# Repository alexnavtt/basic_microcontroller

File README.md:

# Basic Microcontroller

As the name suggests, this repo contains files and code an educational project of mine to build a microcontroller 
breakout board from scratch. I picked the ATMega32u4 for its native USB status, as well as for the wealth of tutorial
and educational material out there on the web. The board itself doesn't have much of a purpose, though anyone is free 
to use it as a reference for a similar project of their own. 

The board has the following features:
  * ATMega32u4 MCU running at 8 MHz
  * USB-C terminal
  * 6-pin ICSP header terminal
  * 1x ADC screw terminal
  * 1x I2C Stemma/QWIIC header
  * 1x RGB LED
  * 5x5 green LED array

There's no particular reason that I run the board at 8 MHz. Generally this MCU is operated at 16 MHz when operating a 
5VDC (which this board is). I just kinda picked 8 on a whim, and as a result I got an additional lesson in recompiling
Arduino bootloaders with modified settings, which I'm honestly really happy with. For an educational project, more things
to learn is always a good thing. Also, placing the LED array on the opposite side but at the same location as the MCU
forced me to get a little creative with wiring, and as my first 4-layer PCB I'm happy with the result 

I have no plans to update this board in the future, but I am thiniking of doing a similar project which an ARM MCU, probably
something simple like an ESP32. We'll see where I end up.

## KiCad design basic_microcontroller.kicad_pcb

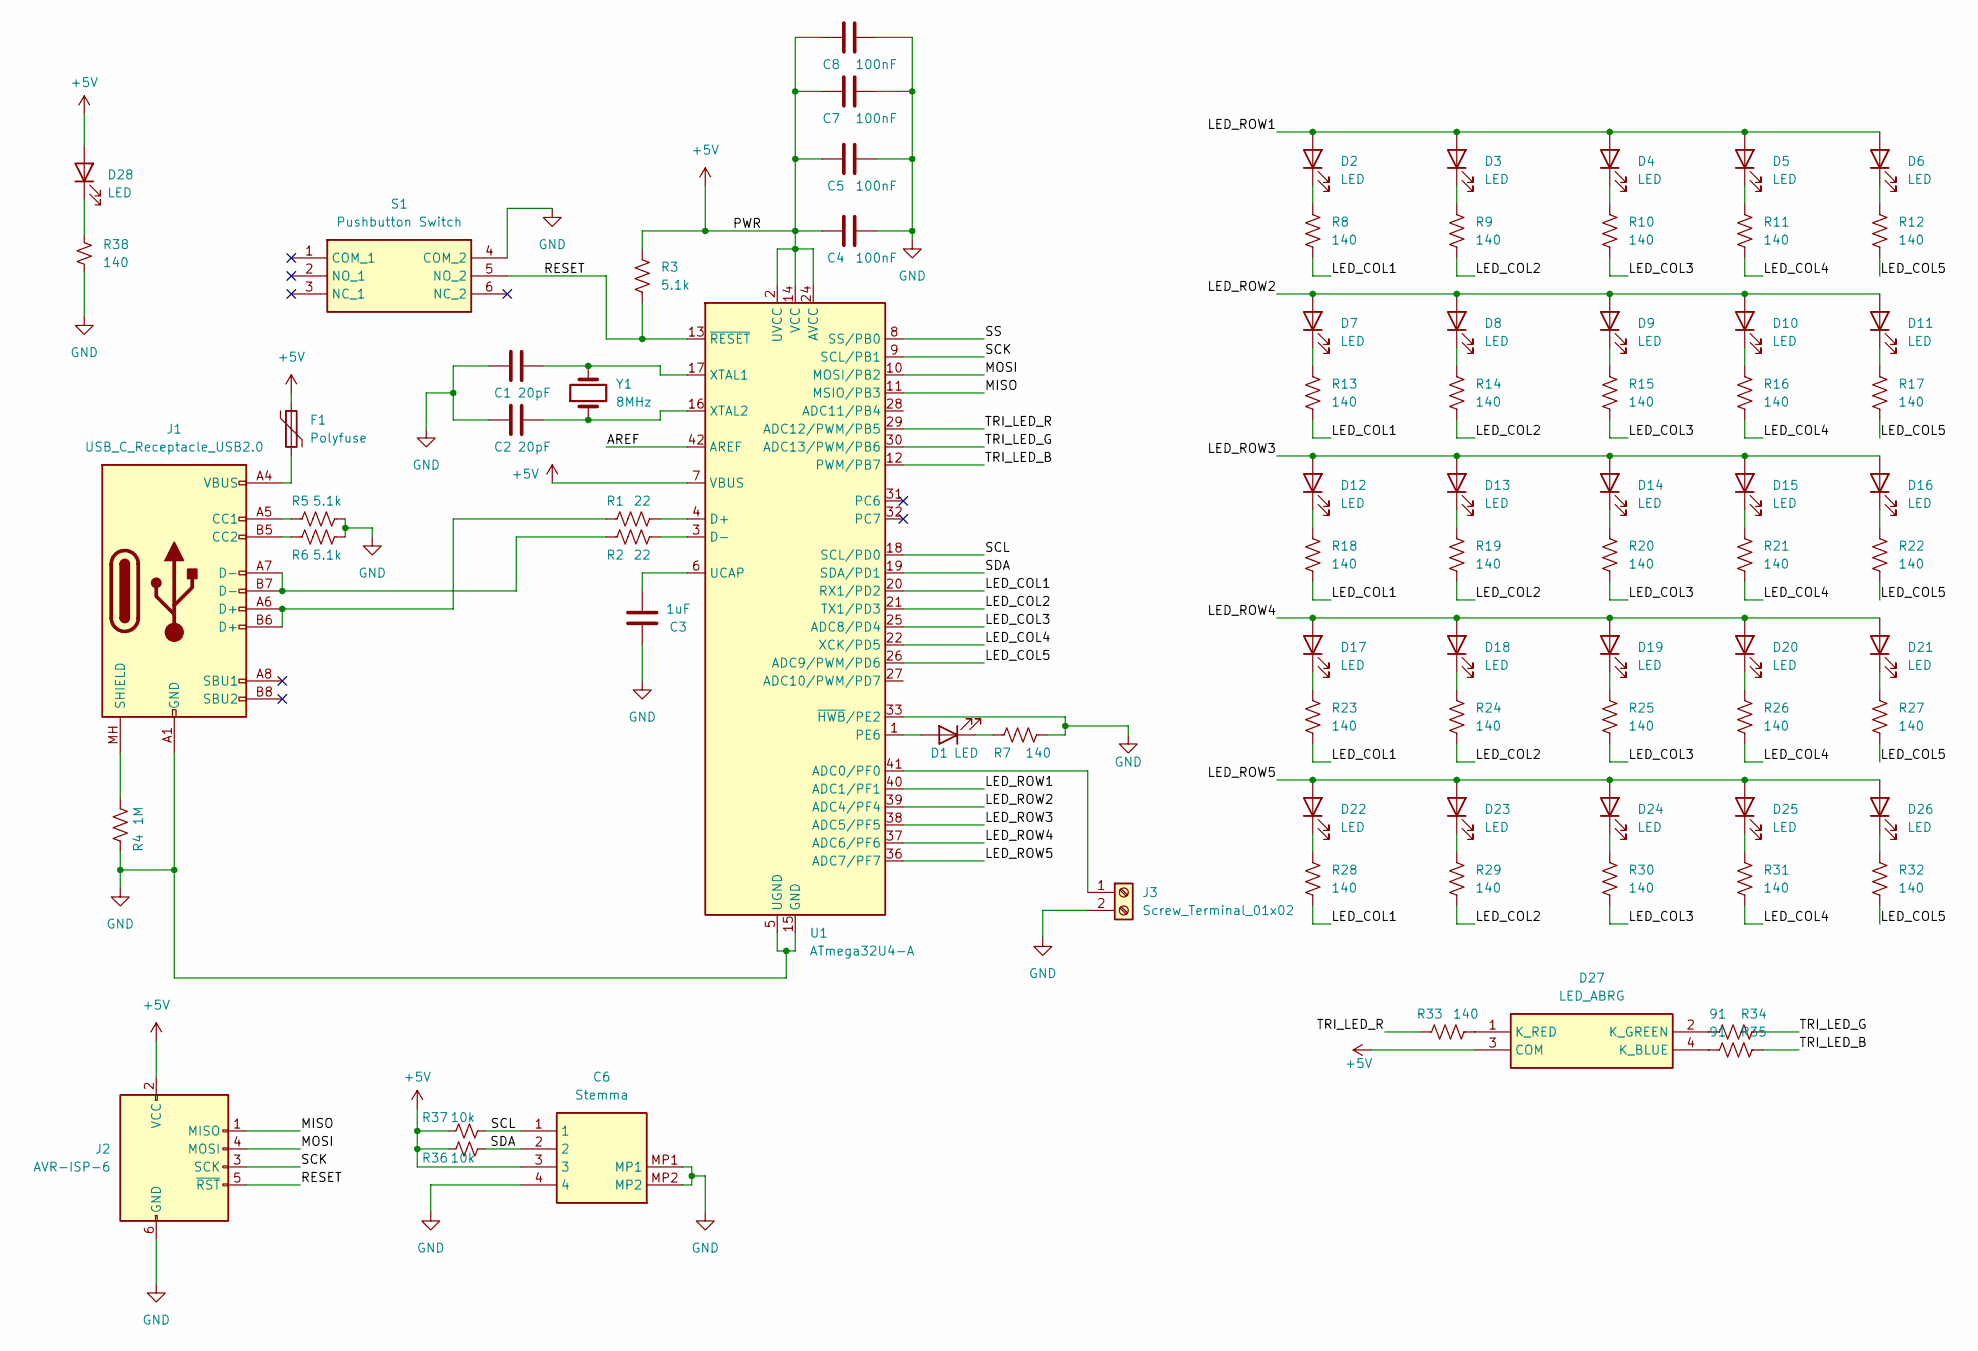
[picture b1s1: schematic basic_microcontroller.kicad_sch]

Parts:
C1, C2: 20pF; C_0603_1608Metric_Pad1.08x0.95mm_HandSolder
C3: 1uF; C_0603_1608Metric_Pad1.08x0.95mm_HandSolder
C4, C5, C7, C8: 100nF; C_0603_1608Metric_Pad1.08x0.95mm_HandSolder
C6: Stemma; stemma; Mouser Part Number 485-4392
D1, D2, D3, D4, D5, D6, D7, D8, D9, D10, D11, D12, D13, D14, D15, D16, D17, D18, D19, D20, D21, D22, D23, D24, D25, D26, D28: LED; LED_0805_2012Metric_Pad1.15x1.40mm_HandSolder
D27: LED_ABRG; RGB LED; Mouser Part Number 743-IN-S85TATRGB
F1: Polyfuse; Fuse_1206_3216Metric_Pad1.42x1.75mm_HandSolder
J1: USB_C_Receptacle_USB2.0; USB480003A
J2: AVR-ISP-6; IDC-Header_2x03_P2.54mm_Vertical
J3: Screw_Terminal_01x02; TerminalBlock_Phoenix_MPT-0,5-2-2.54_1x02_P2.54mm_Horizontal
R1, R2: 22; R_0805_2012Metric_Pad1.20x1.40mm_HandSolder
R3, R5, R6: 5.1k; R_0603_1608Metric_Pad0.98x0.95mm_HandSolder
R4: 1M; R_0805_2012Metric_Pad1.20x1.40mm_HandSolder
R7, R8, R9, R10, R11, R12, R13, R14, R15, R16, R17, R18, R19, R20, R21, R22, R23, R24, R25, R26, R27, R28, R29, R30, R31, R32, R33, R38: 140; R_0805_2012Metric_Pad1.20x1.40mm_HandSolder
R34, R35: 91; R_0805_2012Metric_Pad1.20x1.40mm_HandSolder
R36, R37: 10k; R_0805_2012Metric_Pad1.20x1.40mm_HandSolder
S1: Pushbutton Switch; Mouser Part Number 688-SPEJ110100
U1: ATmega32U4-A; TQFP-44_10x10mm_P0.8mm
Y1: 8MHz; ECS80185PXGMTR

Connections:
+5V: C4.2, C5.2, C6.3, C7.2, C8.2, D27.3 (COM), D28.2 (A), F1.1, J2.2 (VCC), R3.1, R36.1, R37.1, U1.2 (UVCC), U1.7 (VBUS), U1.14 (VCC), U1.24 (AVCC), U1.34 (VCC), U1.44 (AVCC)
/AREF: U1.42 (AREF)
/LED_COL1: R8.2, R13.2, R18.2, R23.2, R28.2, U1.20 (RX1/PD2)
/LED_COL2: R9.2, R14.2, R19.2, R24.2, R29.2, U1.21 (TX1/PD3)
/LED_COL3: R10.2, R15.2, R20.2, R25.2, R30.2, U1.25 (ADC8/PD4)
/LED_COL4: R11.2, R16.2, R21.2, R26.2, R31.2, U1.22 (XCK/PD5)
/LED_COL5: R12.2, R17.2, R22.2, R27.2, R32.2, U1.26 (ADC9/PWM/PD6)
/LED_ROW1: D2.2 (A), D3.2 (A), D4.2 (A), D5.2 (A), D6.2 (A), U1.40 (ADC1/PF1)
/LED_ROW2: D7.2 (A), D8.2 (A), D9.2 (A), D10.2 (A), D11.2 (A), U1.39 (ADC4/PF4)
/LED_ROW3: D12.2 (A), D13.2 (A), D14.2 (A), D15.2 (A), D16.2 (A), U1.38 (ADC5/PF5)
/LED_ROW4: D17.2 (A), D18.2 (A), D19.2 (A), D20.2 (A), D21.2 (A), U1.37 (ADC6/PF6)
/LED_ROW5: D22.2 (A), D23.2 (A), D24.2 (A), D25.2 (A), D26.2 (A), U1.36 (ADC7/PF7)
/MISO: J2.1 (MISO), U1.11 (MSIO/PB3)
/MOSI: J2.4 (MOSI), U1.10 (MOSI/PB2)
/RESET: J2.5 (~RST), R3.2, S1.5 (NO_2), U1.13 (~RESET)
/SCK: J2.3 (SCK), U1.9 (SCL/PB1)
/SCL: C6.1, R37.2, U1.18 (SCL/PD0)
/SDA: C6.2, R36.2, U1.19 (SDA/PD1)
/SS: U1.8 (SS/PB0)
/TRI_LED_B: R35.1, U1.12 (PWM/PB7)
/TRI_LED_G: R34.1, U1.30 (ADC13/PWM/PB6)
/TRI_LED_R: R33.1, U1.29 (ADC12/PWM/PB5)
GND: C1.1, C2.1, C3.1, C4.1, C5.1, C6.4, C6.MP1, C6.MP2, C7.1, C8.1, J1.A1 (GND), J1.A12 (GND), J1.B1 (GND), J1.B12 (GND), J2.6 (GND), J3.2, R4.1, R5.2, R6.2, R7.2, R38.2, S1.4 (COM_2), U1.5 (UGND), U1.15 (GND), U1.23 (GND), U1.33 (~HWB/PE2), U1.35 (GND), U1.43 (GND)
unnamed: D1.2 (A), U1.1 (PE6)
unnamed: D1.1 (K), R7.1
unnamed: D2.1 (K), R8.1
unnamed: D3.1 (K), R9.1
unnamed: D4.1 (K), R10.1
unnamed: D5.1 (K), R11.1
unnamed: D6.1 (K), R12.1
unnamed: D7.1 (K), R13.1
unnamed: D8.1 (K), R14.1
unnamed: D9.1 (K), R15.1
unnamed: D10.1 (K), R16.1
unnamed: D11.1 (K), R17.1
unnamed: D12.1 (K), R18.1
unnamed: D13.1 (K), R19.1
unnamed: D14.1 (K), R20.1
unnamed: D15.1 (K), R21.1
unnamed: D16.1 (K), R22.1
unnamed: D17.1 (K), R23.1
unnamed: D18.1 (K), R24.1
unnamed: D19.1 (K), R25.1
unnamed: D20.1 (K), R26.1
unnamed: D21.1 (K), R27.1
unnamed: D22.1 (K), R28.1
unnamed: D23.1 (K), R29.1
unnamed: D24.1 (K), R30.1
unnamed: D25.1 (K), R31.1
unnamed: D26.1 (K), R32.1
unnamed: D27.4 (K_BLUE), R35.2
unnamed: D27.2 (K_GREEN), R34.2
unnamed: D27.1 (K_RED), R33.2
unnamed: D28.1 (K), R38.1
unnamed: F1.2, J1.A4 (VBUS), J1.A9 (VBUS), J1.B4 (VBUS), J1.B9 (VBUS)
unnamed: J1.A5 (CC1), R5.1
unnamed: J1.B5 (CC2), R6.1
unnamed: J1.A6 (D+), J1.B6 (D+), R1.1
unnamed: J1.A7 (D-), J1.B7 (D-), R2.1
unnamed: J1.MH (SHIELD), R4.2
unnamed: J3.1, U1.41 (ADC0/PF0)
unnamed: R1.2, U1.4 (D+)
unnamed: R2.2, U1.3 (D-)
unnamed: C3.2, U1.6 (UCAP)
unnamed: C1.2, U1.17 (XTAL1), Y1.2
unnamed: C2.2, U1.16 (XTAL2), Y1.1

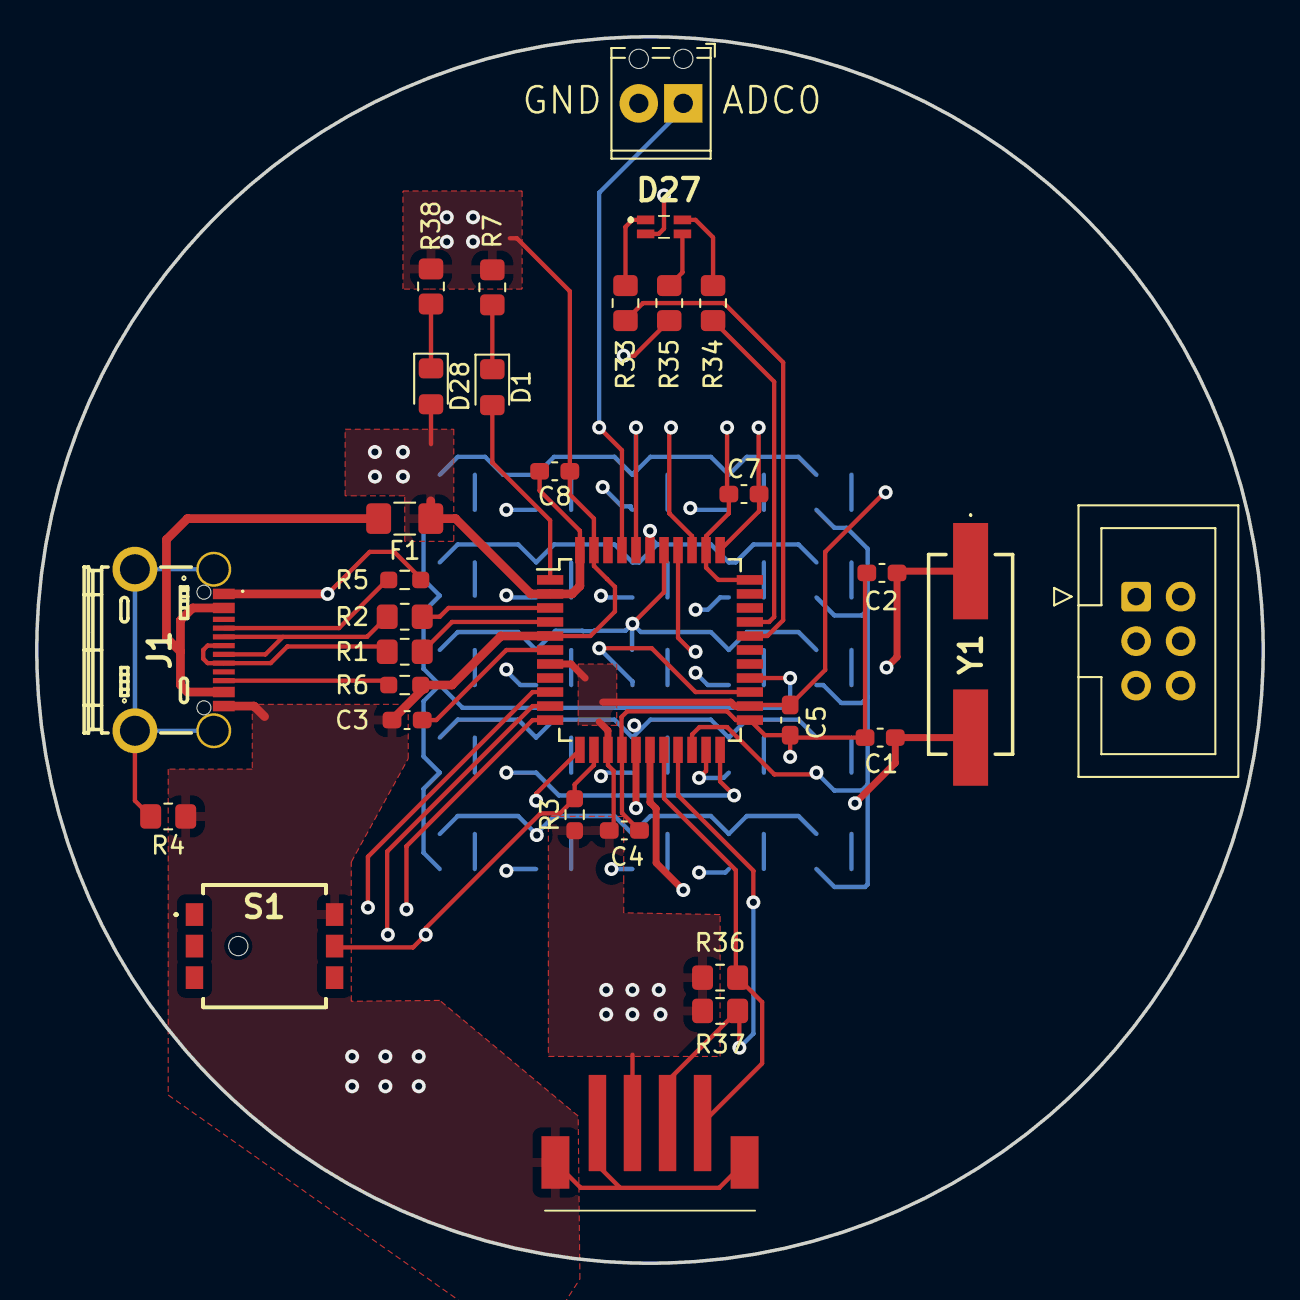
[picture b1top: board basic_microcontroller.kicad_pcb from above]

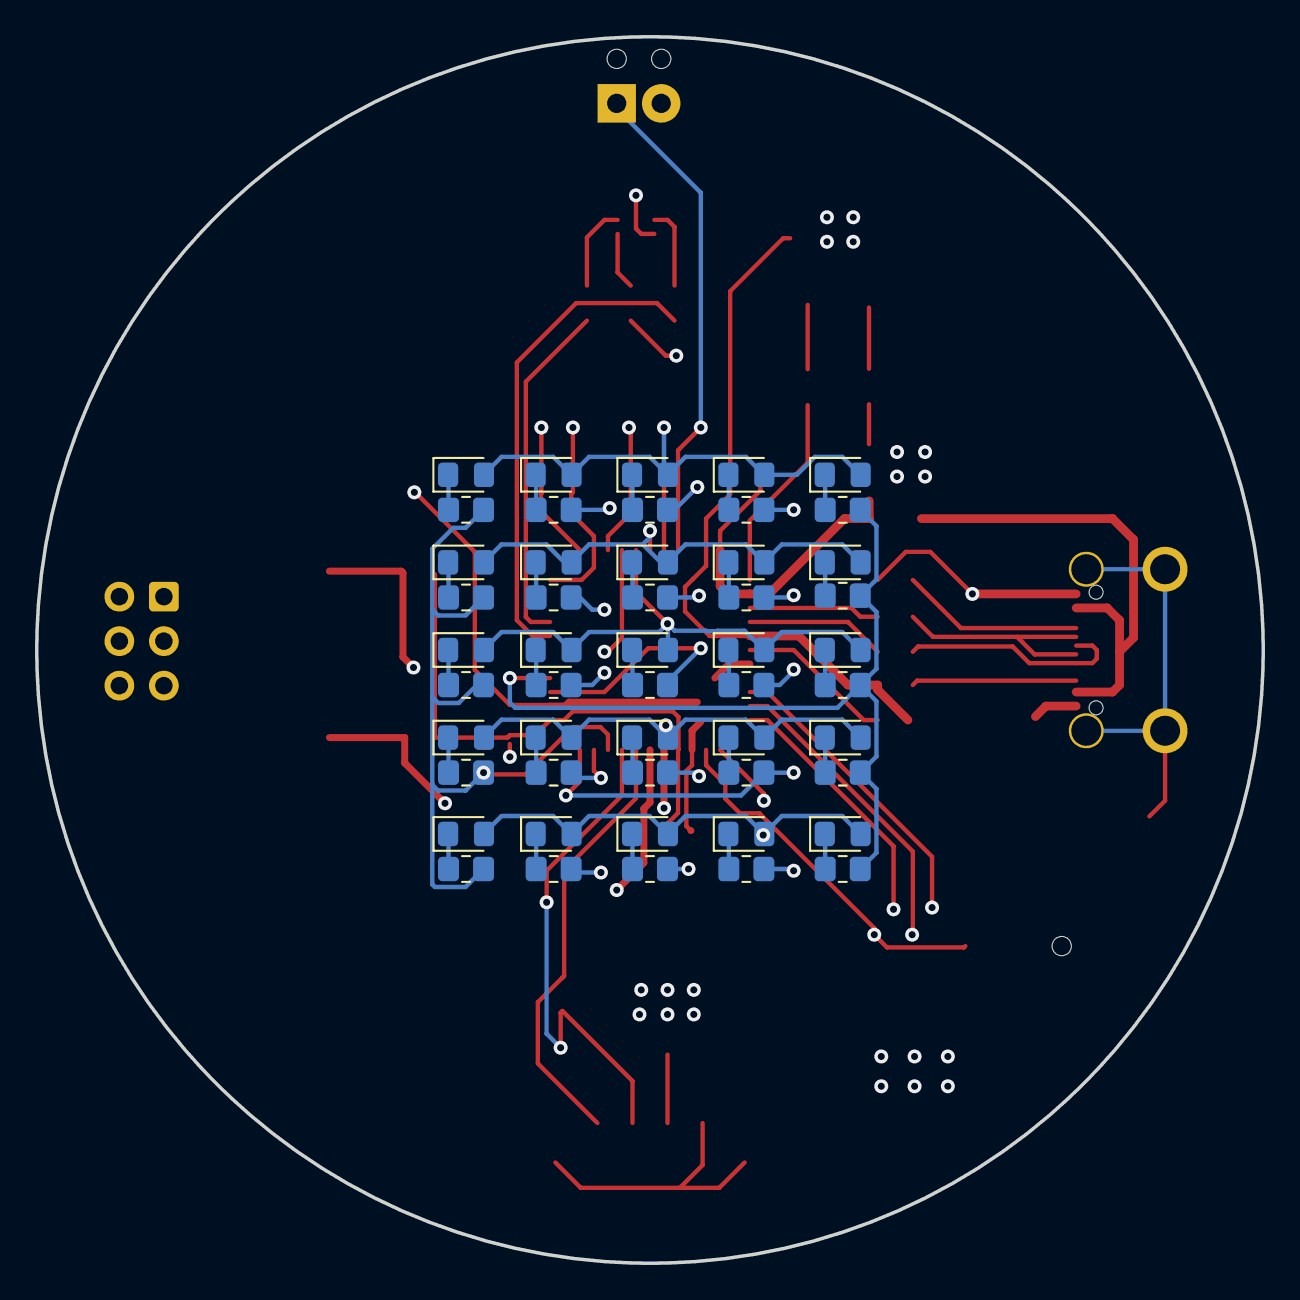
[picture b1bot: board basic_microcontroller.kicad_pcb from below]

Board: 4 copper layers, 70.0 x 70.0 mm, 81 parts (50 on the bottom side), 64 nets.

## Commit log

2023-07-30 Update gitignore
2023-07-30 Fixed wiring on button
